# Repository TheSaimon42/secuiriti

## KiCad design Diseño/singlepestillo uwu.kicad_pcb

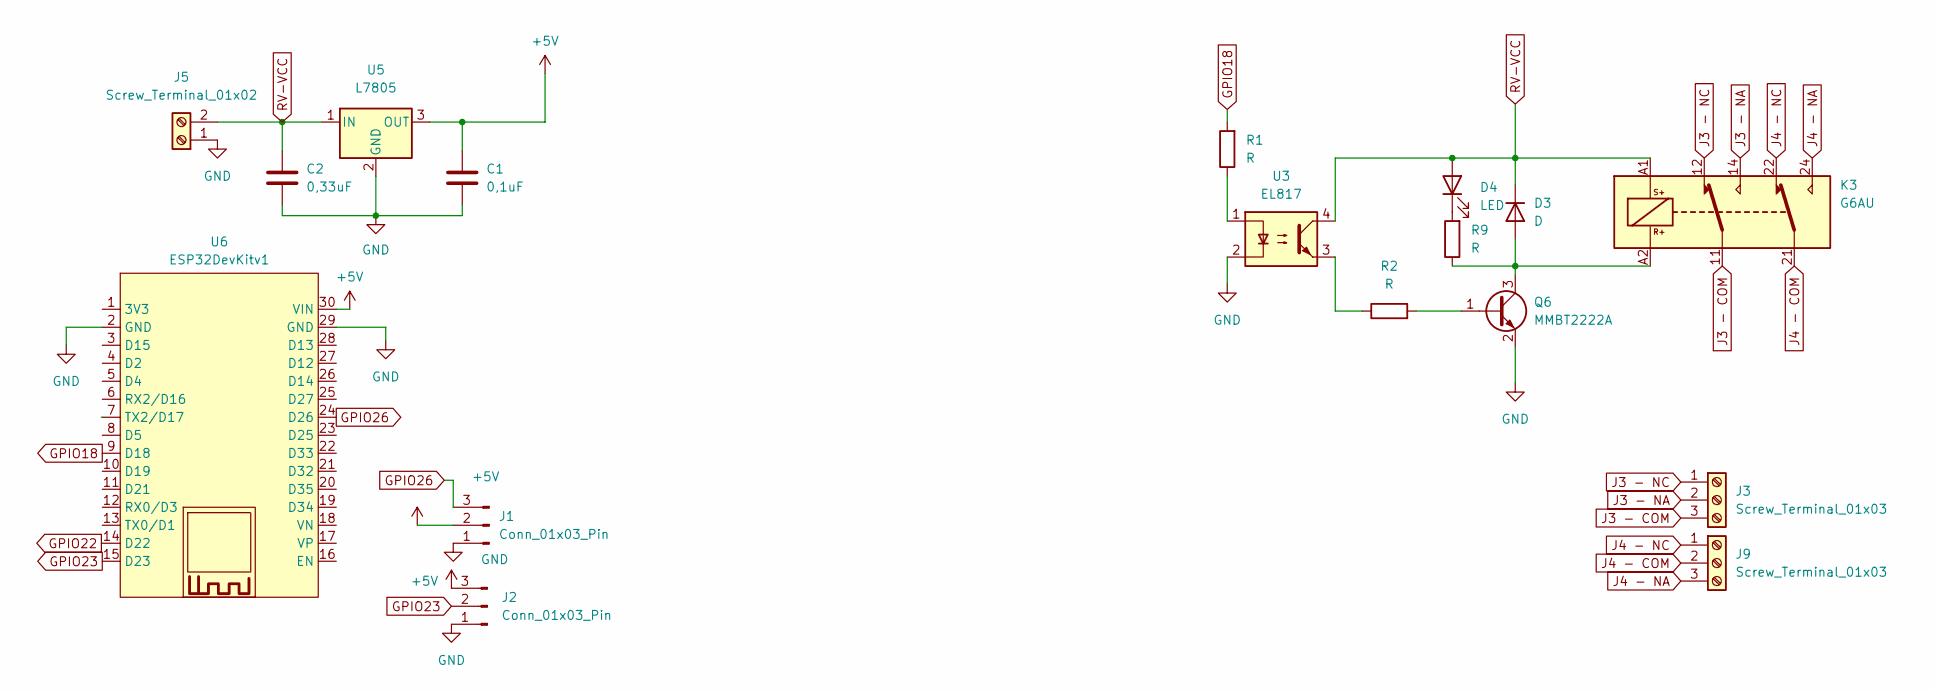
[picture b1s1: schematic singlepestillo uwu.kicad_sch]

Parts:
C1: 0,1uF; C_Axial_L3.8mm_D2.6mm_P7.50mm_Horizontal
C2: 0,33uF; C_Axial_L3.8mm_D2.6mm_P7.50mm_Horizontal
D3: D; D_SMA
D4: LED; LED_D5.0mm_Clear
J1, J2: Conn_01x03_Pin; PinHeader_1x03_P2.54mm_Vertical
J3, J9: Screw_Terminal_01x03; TerminalBlock_Xinya_XY308-2.54-3P_1x03_P2.54mm_Horizontal
J5: Screw_Terminal_01x02; TerminalBlock_bornier-2_P5.08mm
K3: G6AU; Relay_DPDT_Omron_G6A
Q6: MMBT2222A; SOT-23
R1, R2, R9: R; R_0805_2012Metric
U3: EL817; DIP-4_W7.62mm
U5: L7805; TO-3P-3_Vertical
U6: ESP32DevKitv1; ESP32-C3-DevKitM-1

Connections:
+5V: C1.1, J1.2, J2.3, U5.3 (OUT), U6.30 (VIN)
GND: C1.2, C2.2, J1.1, J2.1, J5.1, Q6.2 (E), U3.2, U5.2 (GND), U6.2 (GND), U6.29 (GND)
GPIO18: R1.2, U6.9 (D18)
GPIO22: U6.14 (D22)
GPIO23: J2.2, U6.15 (D23)
GPIO26: J1.3, U6.24 (D26)
J3 - COM: J3.3, K3.11
J3 - NA: J3.2, K3.14
J3 - NC: J3.1, K3.12
J4 - COM: J9.2, K3.21
J4 - NA: J9.3, K3.24
J4 - NC: J9.1, K3.22
unnamed: D3.2 (A), K3.A2, Q6.3 (C), R9.1
unnamed: D4.1 (K), R9.2
unnamed: Q6.1 (B), R2.2
unnamed: R1.1, U3.1
unnamed: R2.1, U3.3
RV-VCC: C2.1, D3.1 (K), D4.2 (A), J5.2, K3.A1, U3.4, U5.1 (IN)

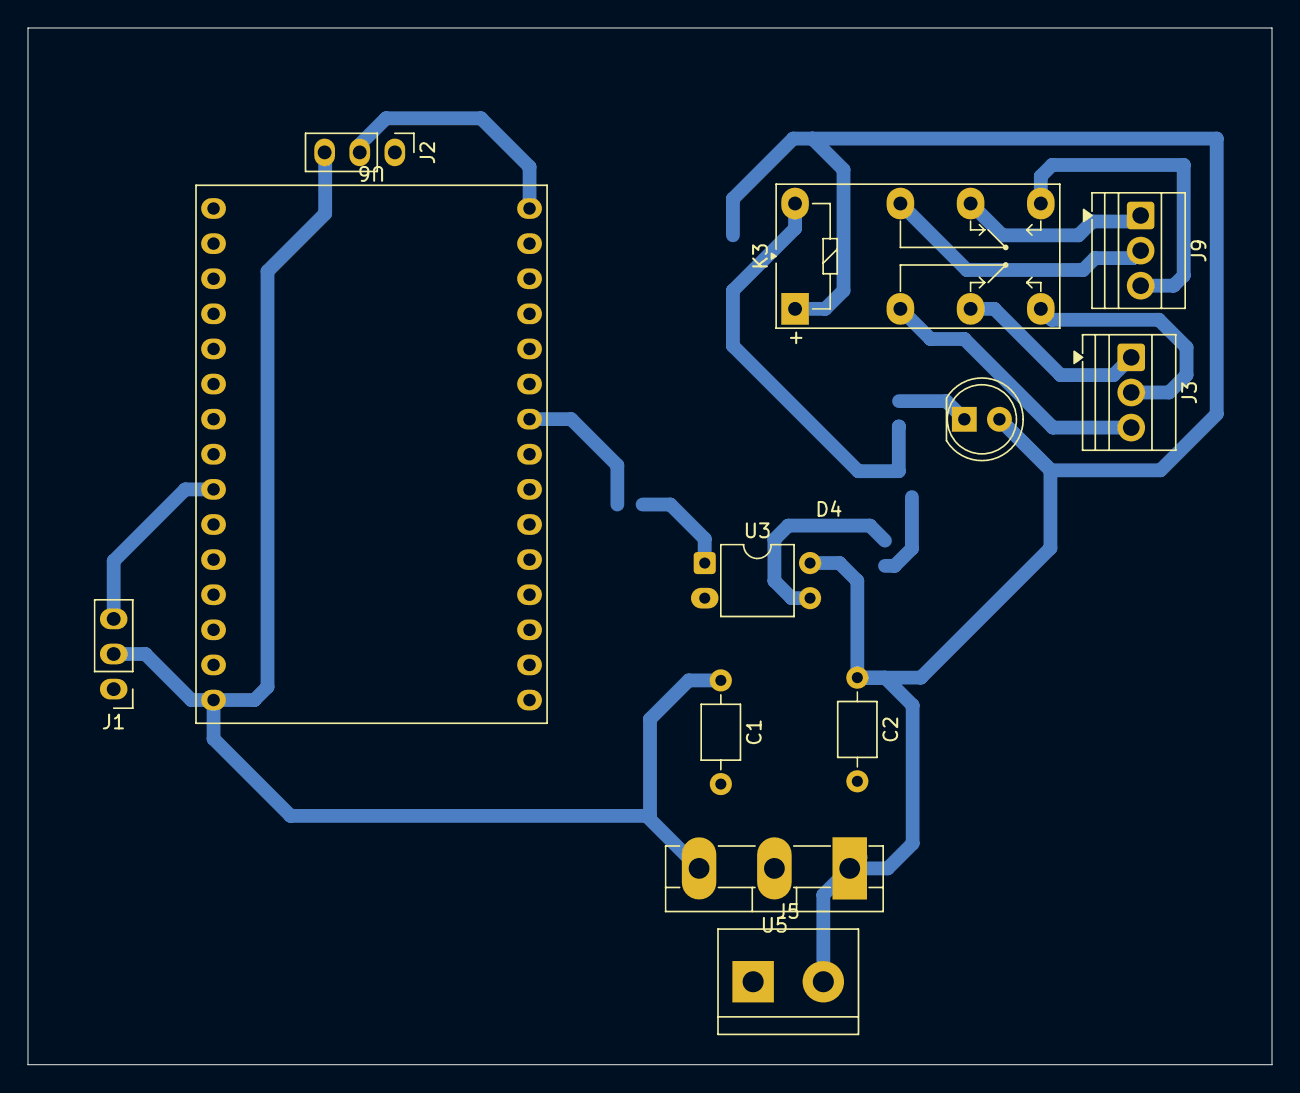
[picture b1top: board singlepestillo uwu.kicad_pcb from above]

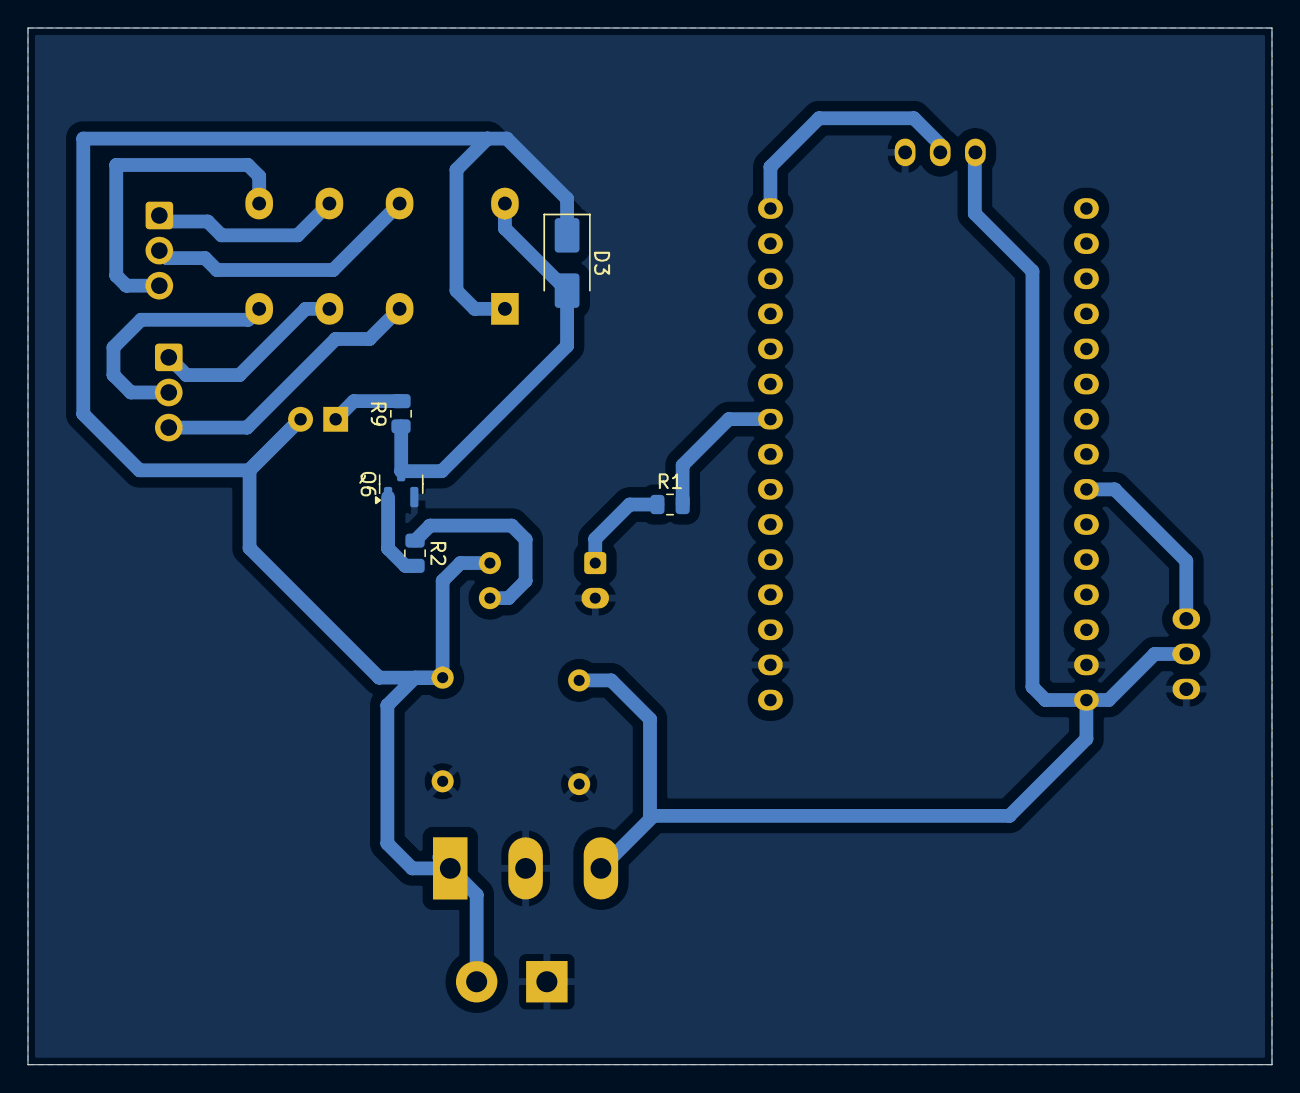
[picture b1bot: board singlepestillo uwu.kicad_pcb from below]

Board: 2 copper layers, 90.0 x 75.0 mm, 17 parts (5 on the bottom side), 17 nets.

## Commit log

2025-08-22 inicio proyecto
2025-08-22 acomodo del proyecto
2025-09-05 codigo preliminar
2025-09-09 avance pcb armado
2025-09-09 avance pcb
2025-09-19 correcion pcb y avance codigo
2025-09-30 Primer modelo final pcb
2025-10-07 Cambios en el amplificador del pcb, programacion actualizada
2025-10-07 Optimizacion diseño del pcb
